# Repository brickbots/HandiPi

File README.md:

# HandiPi

Handheld RPI4 based computer with 36-key tactile keyboard and display

## What is it?

Glad you asked.. it's a fully functional linux computer with:
* A Raspberry Pi 4
* Custom 36-key keyboard with 5 way directional buton based around an Atmega328
* 4.3" DSI touchscreen display
* PiSugar power controller with 5000mah battery

It runs for about 4 hours with general terminal use and is pretty useful on it's own, but you can hook 
up external monitors and other USB peripherals if you need more screen or typing space.

The keyboard runs QMK and interfaces to the Pi via USB, so it's fully configurable.  I really like the
[Miryoku](https://github.com/manna-harbour/miryoku) layout and use it on all my keyboards...so that's
what the physical button layout is based around.  The switches are Diptronic DTS63K tactiles with 1Nm 
of actuation force.  They look the same as the generic ones, but it's worth the few extra dollars as 
they feel so much better to type on.  It's still a thumb-typing experience, but the limited number of
keys and the well thought out layering system of Miryoku makes it a suprisingly useful keyboard!

## Oh god, why?

Well.. it all started when I picked up the PCB's for the 
[PICOmputer](https://www.tindie.com/products/bobricius/picomputer-rp2040-raspbbery-pico-qwerty-devkit/) 
made by [Bobricius](https://www.tindie.com/stores/bobricius/).  It's a sort of carrier board for the 
Raspberry Pi PICO that includes a keyboard using 6mm pushbutton tactile switches and a display.  It's 
simple, but it really opens up some fun potential.  I ended up 3d printing a case for mine and adding
a battery with charging to make it a neat little toy to play with.  Along the way, I was really
impressed with how well the keyboard actually worked.. even though I didn't follow his advice and bought
cheaper switches with higher actuation force.

When it came time to replace the Orange Pi based desktop PC I used at my workbench I grabbed the RPI4 I ordered
early in the pandemic and had been hording.  I was just going to put it in a boring case, but then I got 
to thinking about the PICOmputer and wondering if I could build a case with a screen and keyboard.  I'd 
still use the computer with a monitor, keyboard and trackball at my desk most of the time, but I could 
grab it and have my workbench computer with me if I wanted to go hack at a friends house or makerspace.

So that's where the idea came from, and the rest was just balancing the screen size with portability and
thinking hard about thumb-typing layouts....

## Designing a tiny keyboard

I've built a good number of keyboards in my time, and even [designed](https://github.com/brickbots/chocV)
a [couple](https://github.com/brickbots/slabv).  Most of the keyboards I've built rely on a pre-assembled 
Pro-Micro style controller, but I just didn't think I'd have the space to use that trick here.  There are 
many good refrence designs for the basic AtMega circuit, and I can
solder surface mount diodes okay, but I realy didn't think I'd have the skills to do a fine-pitch 
AtMega surface mount package without a lot of pain and suffering.  It was then that I remembered the first
keyboard I ever built.... the [Plaid](https://github.com/hsgw/plaid)!

The Plaid is a really neat 4x12 ortho keyboard built using ALL throughhole components!  It uses virtual
usb on an AtMega328 which is one of the few AtMega versions availabe in a DIPP package.  With this 
schematic in hand and information about the boot loader HSGW used, I started designing a new PCB.

This is actually version 2... for the first one I thought I understood more than I did and left off the 3.6v
zener diodes on the USB data lines.  BTW, USB actually uses 3.6v signals!  Who knew?  I didn't know, so I 
thought the zeners were for overvoltage protection... They are not and many USB hubs/controllers won't work 
with 5v signal lines.  So, you need those if you are using a 5v MCU.

Here's a good place to thank [PCBWay](https://www.pcbway.com) for covering the cost of these boards.  Liam
reached out to me after seeing the [Framedeck project](https://github.com/brickbots/framedeck) with it's
custom keyboard/trackball PCB and asked me to give PCBWay a try with my next project.  I did, and they gave 
me a coupon to cover the cost, which was right nice of them.  The PCB's are not overly complicated, but the 
pricing was in line with other vendors, they arrived quickly, looked nice and clean and were fabbed to spec.
Overall, a nice experience and I'll definitely consider them again in the future.

So after two revisions, everything worked and it looks nice and tidy with the 1mm top PCB to cover the guts
and present nice legends.

## OS and Navigation
This little bad-boy runs Raspberry Pi OS, a Debian derivitive, and I use i3 as my window manager.  This is
a great tiling window manager that I run on all my linux systems, but it's particularly well suited for 
resource limited machines as it's very light weight.  It's also very keyboard friendly, which helps as 
this unit does not have a great pointing device.  The touchscreen works okay for some things, and the 
Miryoku layout has support for mouse keys on a layer (which can be used with hjkl or the directional button)
, but I prefer keyboard interaction where possible.

i3 does have a good number of multi-key combos to get stuff done, and these are tricky with just two thumbs. 
It's possible to get another finger in the mix and still hold on, but I ended up using the directional button 
for a lot of the multi-key directional bits like focus left/right/up/down, resizing windows, or switching
desktops.  The directions are mapped to mod-h,j,k,l which will change window focus by default.  I can combine
this shift to move windows.  If I hold down the center directional button, the four directions change
between four desktops, and I can combine this with shift to move a window to a specific desktop!

There are some other less common combos (like defining vertical/horizontal splits) that can always be 
accessed using the actual key combos

## More info

Here's a photo of the back of the unit showing the HDMI, audio output, and charging port of the PiSugar. 
To the left (in the photo, right side of the unit) is the one available USB port on the RPI 4.  To make 
the whole thing thinner, I removed the ethernet jack and double USB ports.  One of the usb pinouts is 
run internally to talk to the keyboard, and I put a single-high USB jack on the other for external 
connections.

If you'd like to learn more about how this was all put together check these links below:

* [Parts List](docs/BOM.md)
* [Build Tour](docs/build.md)

## Copyright and License

Copyright (c) 2022 Richard Sutherland. All rights reserved.

All files are licensed under MIT license
see the [LICENSE](LICENSE) for more information.

<a href='https://ko-fi.com/brickbots' target='_blank'>

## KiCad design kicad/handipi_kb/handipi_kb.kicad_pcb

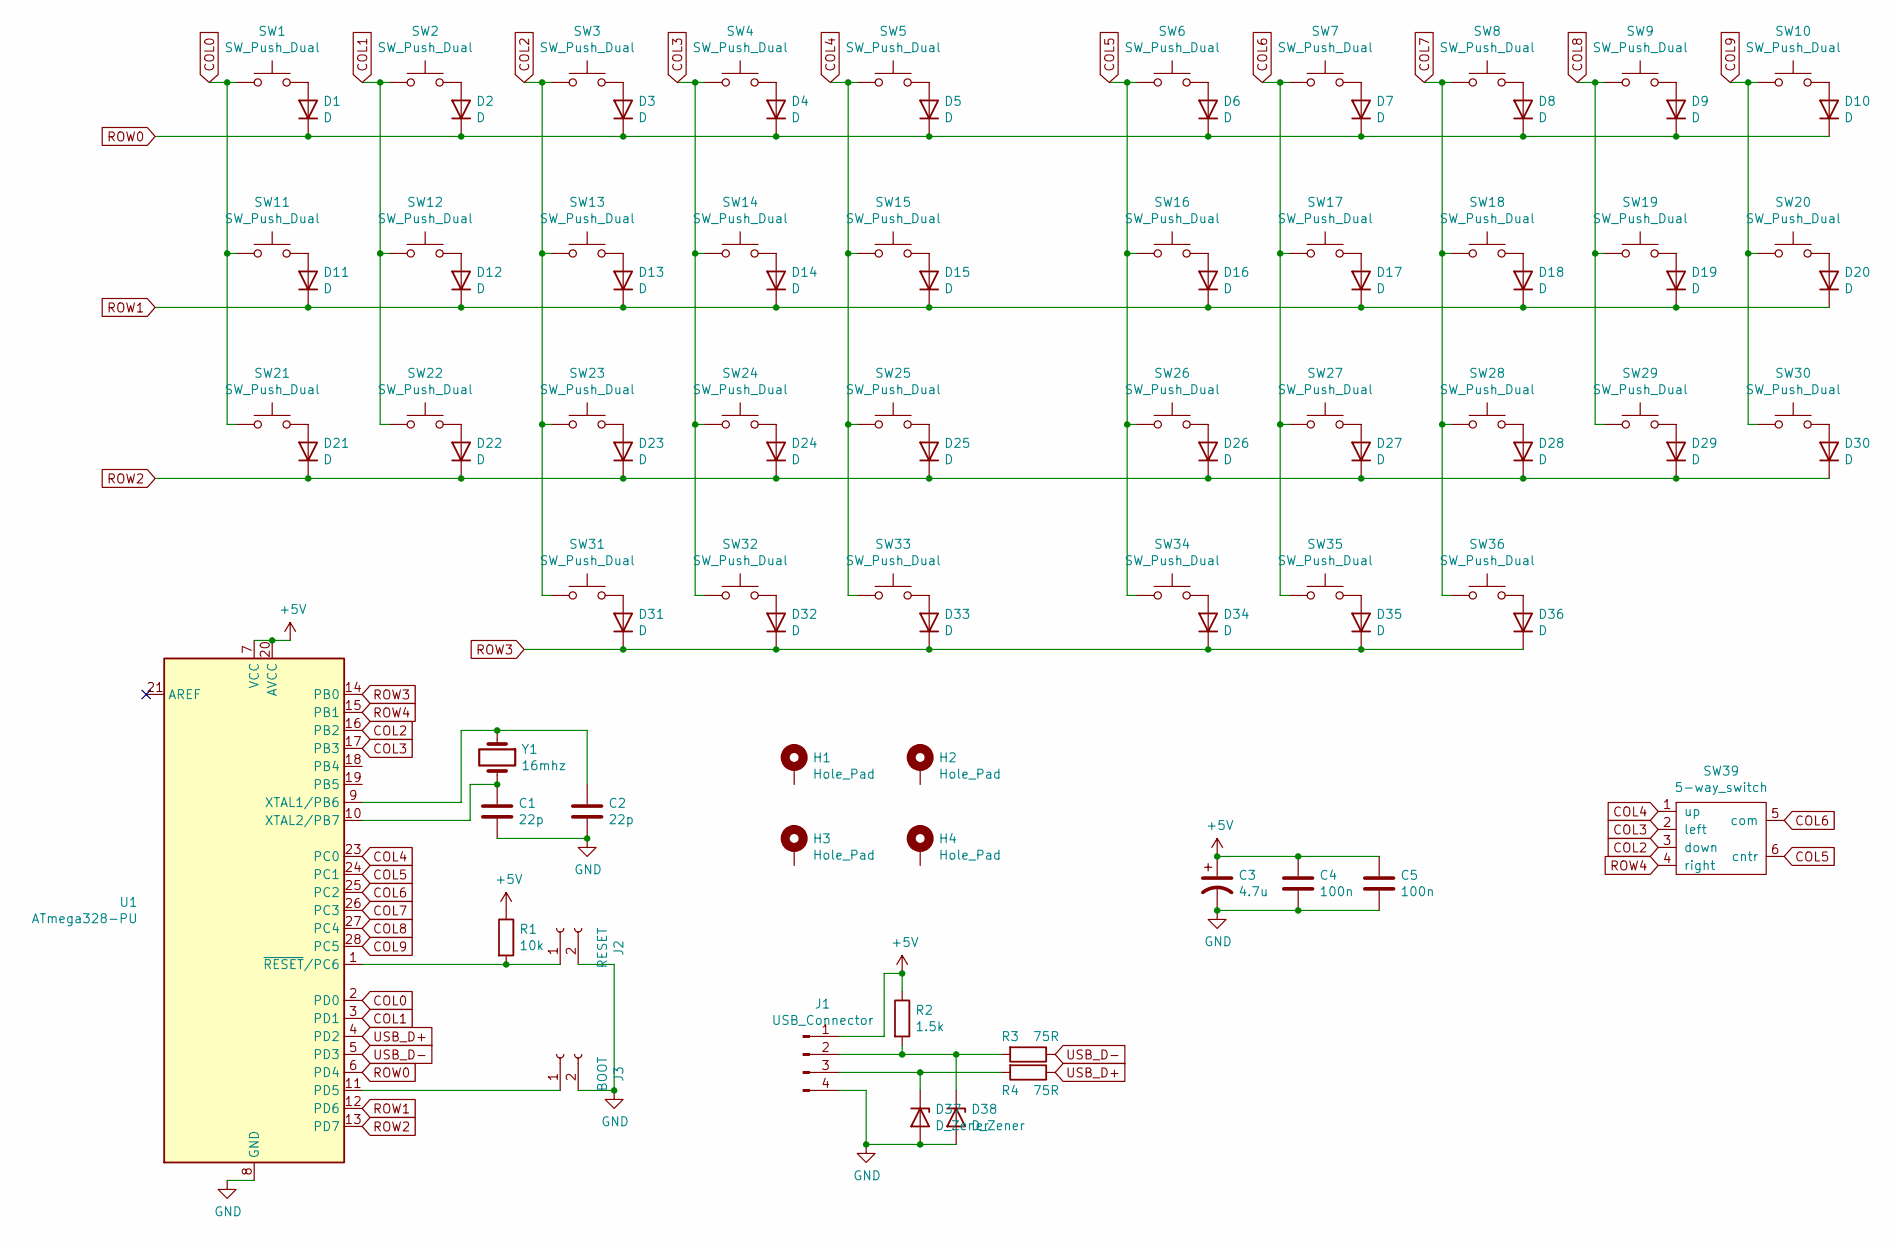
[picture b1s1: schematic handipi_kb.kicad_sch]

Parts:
C1, C2: 22p; C_Disc_D3.0mm_W2.0mm_P2.50mm
C3: 4.7u; CP_Radial_D4.0mm_P1.50mm
C4, C5: 100n; C_Disc_D4.3mm_W1.9mm_P5.00mm
D1, D2, D3, D4, D5, D6, D7, D8, D9, D10, D11, D12, D13, D14, D15, D16, D17, D18, D19, D20, D21, D22, D23, D24, D25, D26, D27, D28, D29, D30, D31, D32, D33, D34, D35, D36: D; D_SOD-123
D37, D38: D_Zener; D_A-405_P7.62mm_Horizontal
H1, H2, H3, H4: Hole_Pad; Mount_M2
J1: USB_Connector; PinHeader_1x04_P1.27mm_Vertical
J2: RESET; PinHeader_1x02_P1.27mm_Vertical
J3: BOOT; PinHeader_1x02_P1.27mm_Vertical
R1: 10k; R_Axial_DIN0207_L6.3mm_D2.5mm_P10.16mm_Horizontal
R2: 1.5k; R_Axial_DIN0207_L6.3mm_D2.5mm_P10.16mm_Horizontal
R3, R4: 75R; R_Axial_DIN0207_L6.3mm_D2.5mm_P10.16mm_Horizontal
SW1, SW2, SW3, SW4, SW5, SW6, SW7, SW8, SW9, SW10, SW11, SW12, SW13, SW14, SW15, SW16, SW17, SW18, SW19, SW20, SW21, SW22, SW23, SW24, SW25, SW26, SW27, SW28, SW29, SW30, SW31, SW32, SW33, SW34, SW35, SW36: SW_Push_Dual; SW_PUSH_6mm_with_hole
SW39: 5-way_switch; switch_5way
U1: ATmega328-PU; DIP-28_W7.62mm
Y1: 16mhz; Crystal_HC18-U_Vertical

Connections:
+5V: C3.1, C4.1, C5.1, J1.1, R1.1, R2.1, U1.7 (VCC), U1.20 (AVCC)
COL0: SW1.1, SW11.1, SW21.1, U1.2 (PD0)
COL1: SW2.1, SW12.1, SW22.1, U1.3 (PD1)
COL2: SW3.1, SW13.1, SW23.1, SW31.1, SW39.3 (down), U1.16 (PB2)
COL3: SW4.1, SW14.1, SW24.1, SW32.1, SW39.2 (left), U1.17 (PB3)
COL4: SW5.1, SW15.1, SW25.1, SW33.1, SW39.1 (up), U1.23 (PC0)
COL5: SW6.1, SW16.1, SW26.1, SW34.1, SW39.6 (cntr), U1.24 (PC1)
COL6: SW7.1, SW17.1, SW27.1, SW35.1, SW39.5 (com), U1.25 (PC2)
COL7: SW8.1, SW18.1, SW28.1, SW36.1, U1.26 (PC3)
COL8: SW9.1, SW19.1, SW29.1, U1.27 (PC4)
COL9: SW10.1, SW20.1, SW30.1, U1.28 (PC5)
GND: C1.2, C2.2, C3.2, C4.2, C5.2, D37.2 (A), D38.2 (A), J1.4, J2.2, J3.2, U1.8 (GND), U1.22 (GND)
unnamed: C1.1, U1.10 (XTAL2/PB7), Y1.2
unnamed: C2.1, U1.9 (XTAL1/PB6), Y1.1
unnamed: D1.2 (A), SW1.2
unnamed: D2.2 (A), SW2.2
unnamed: D3.2 (A), SW3.2
unnamed: D4.2 (A), SW4.2
unnamed: D5.2 (A), SW5.2
unnamed: D6.2 (A), SW6.2
unnamed: D7.2 (A), SW7.2
unnamed: D8.2 (A), SW8.2
unnamed: D9.2 (A), SW9.2
unnamed: D10.2 (A), SW10.2
unnamed: D11.2 (A), SW11.2
unnamed: D12.2 (A), SW12.2
unnamed: D13.2 (A), SW13.2
unnamed: D14.2 (A), SW14.2
unnamed: D15.2 (A), SW15.2
unnamed: D16.2 (A), SW16.2
unnamed: D17.2 (A), SW17.2
unnamed: D18.2 (A), SW18.2
unnamed: D19.2 (A), SW19.2
unnamed: D20.2 (A), SW20.2
unnamed: D21.2 (A), SW21.2
unnamed: D22.2 (A), SW22.2
unnamed: D23.2 (A), SW23.2
unnamed: D24.2 (A), SW24.2
unnamed: D25.2 (A), SW25.2
unnamed: D26.2 (A), SW26.2
unnamed: D27.2 (A), SW27.2
unnamed: D28.2 (A), SW28.2
unnamed: D29.2 (A), SW29.2
unnamed: D30.2 (A), SW30.2
unnamed: D31.2 (A), SW31.2
unnamed: D32.2 (A), SW32.2
unnamed: D33.2 (A), SW33.2
unnamed: D34.2 (A), SW34.2
unnamed: D35.2 (A), SW35.2
unnamed: D36.2 (A), SW36.2
unnamed: D37.1 (K), J1.3, R4.2
unnamed: D38.1 (K), J1.2, R2.2, R3.2
unnamed: J2.1, R1.2, U1.1 (~RESET/PC6)
unnamed: J3.1, U1.11 (PD5)
ROW0: D1.1 (K), D2.1 (K), D3.1 (K), D4.1 (K), D5.1 (K), D6.1 (K), D7.1 (K), D8.1 (K), D9.1 (K), D10.1 (K), U1.6 (PD4)
ROW1: D11.1 (K), D12.1 (K), D13.1 (K), D14.1 (K), D15.1 (K), D16.1 (K), D17.1 (K), D18.1 (K), D19.1 (K), D20.1 (K), U1.12 (PD6)
ROW2: D21.1 (K), D22.1 (K), D23.1 (K), D24.1 (K), D25.1 (K), D26.1 (K), D27.1 (K), D28.1 (K), D29.1 (K), D30.1 (K), U1.13 (PD7)
ROW3: D31.1 (K), D32.1 (K), D33.1 (K), D34.1 (K), D35.1 (K), D36.1 (K), U1.14 (PB0)
ROW4: SW39.4 (right), U1.15 (PB1)
USB_D+: R4.1, U1.4 (PD2)
USB_D-: R3.1, U1.5 (PD3)

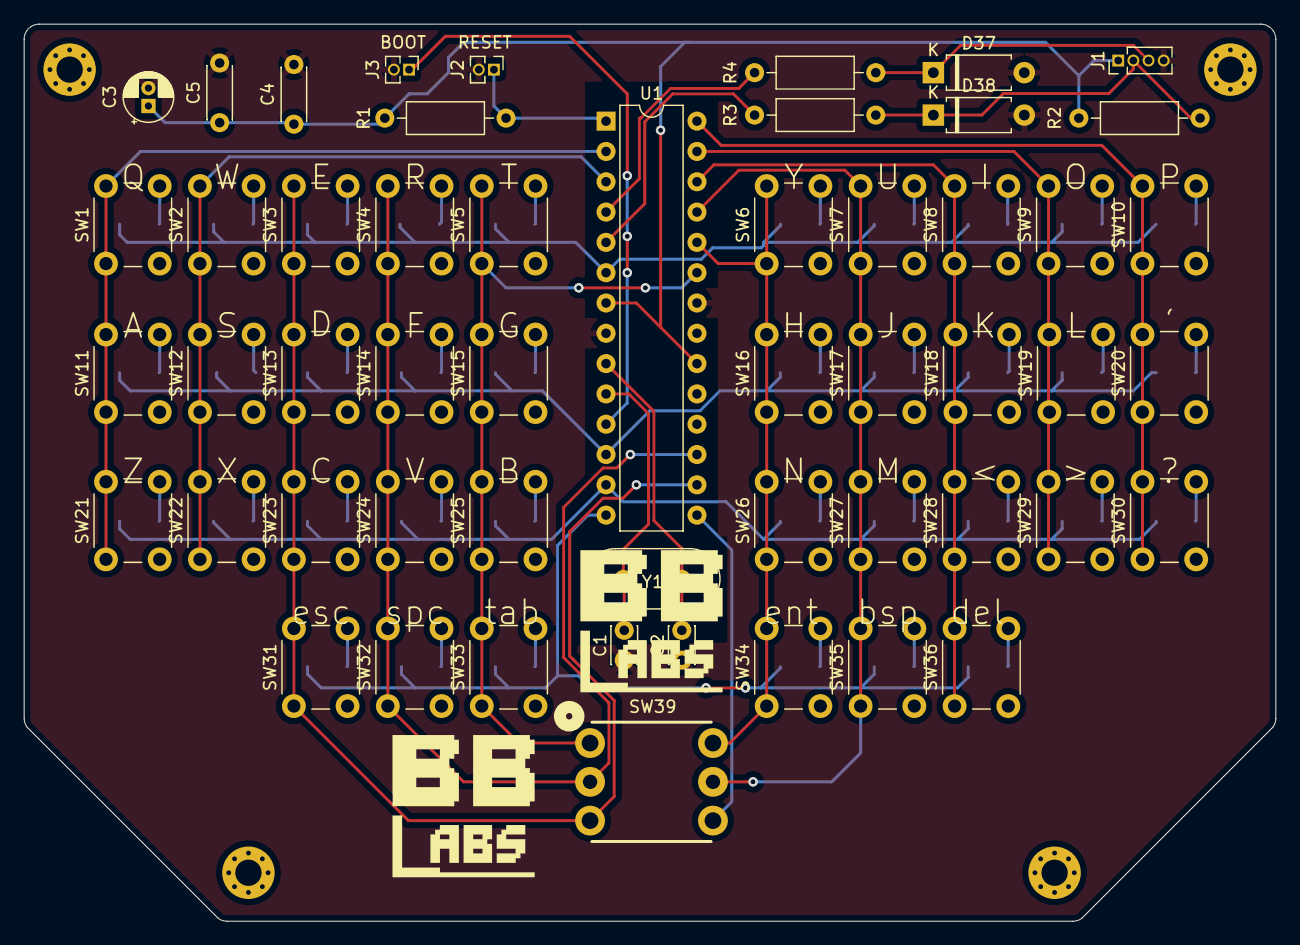
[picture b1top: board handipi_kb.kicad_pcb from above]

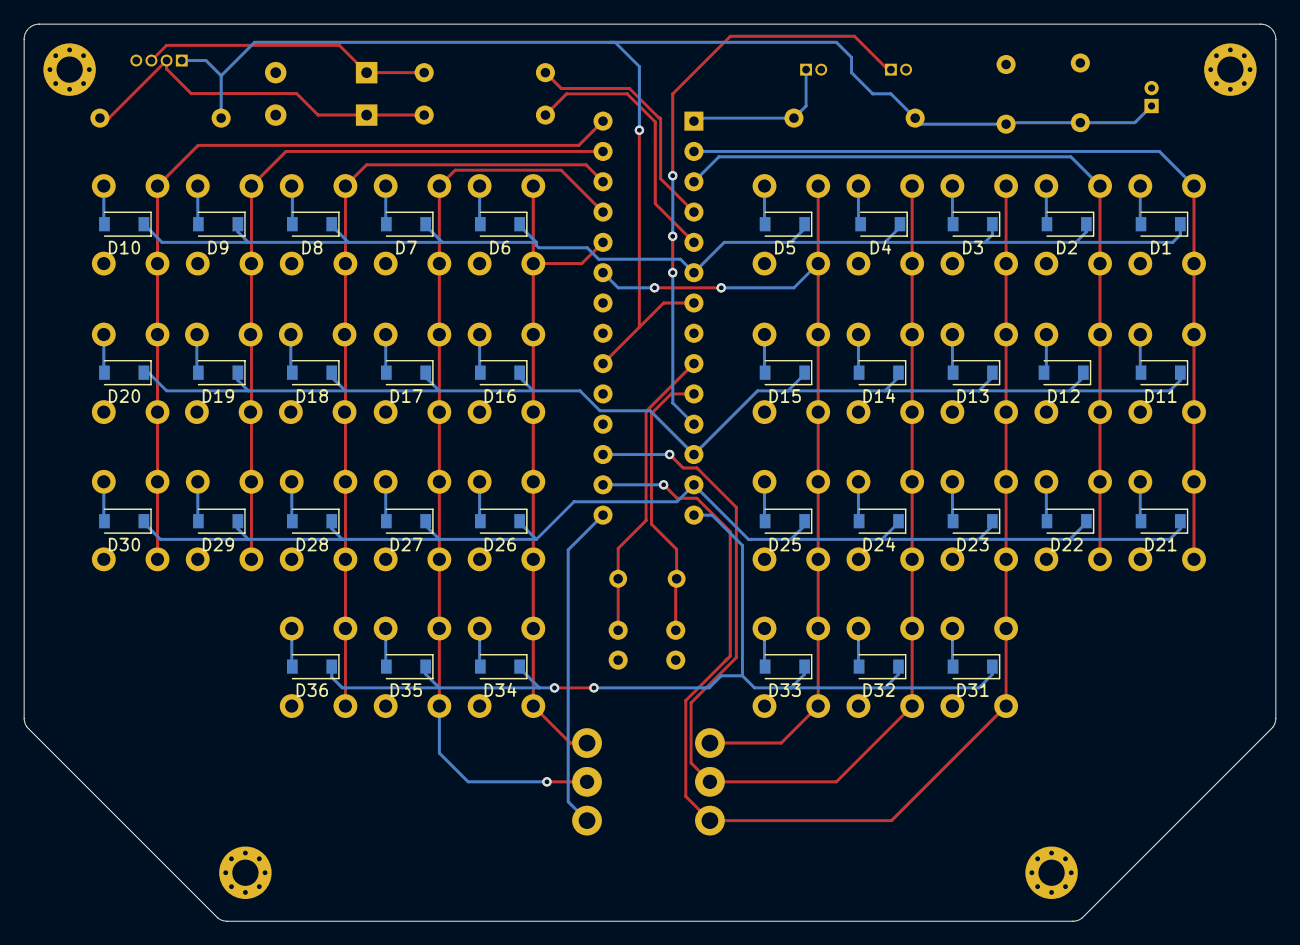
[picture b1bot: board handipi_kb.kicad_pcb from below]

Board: 2 copper layers, 104.9 x 75.2 mm, 95 parts (36 on the bottom side), 61 nets.

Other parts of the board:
LOGO1: LOGO1; bblabs_logo_sml
PCBLogo: PCBLogo; bblabs_logo_sml

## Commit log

2022-06-04 WIP kb
2022-07-31 Clean up structure and V1
2022-08-19 Starting docs
2022-08-19 Continuing docs...
2022-08-19 Getting there...
2022-08-23 Build tour
2022-08-23 Typos and such
2022-10-04 Fix Newton meters typo
2023-01-24 Buy me a coffee
2023-04-13 Fix footprint for directional switch
2023-10-08 Fix ground connection for col 6
